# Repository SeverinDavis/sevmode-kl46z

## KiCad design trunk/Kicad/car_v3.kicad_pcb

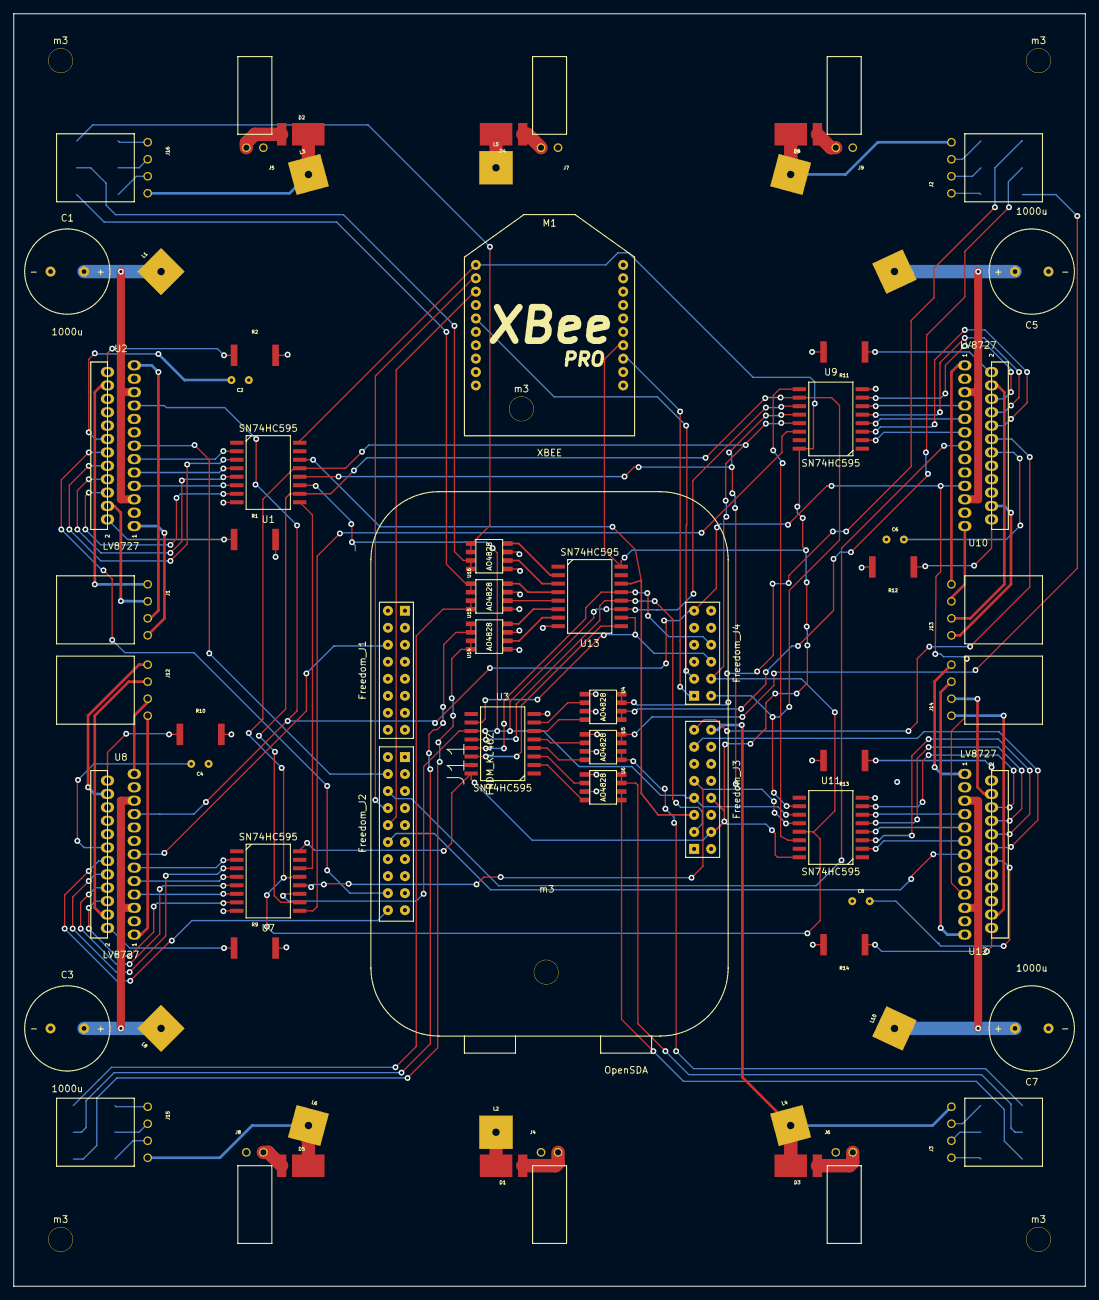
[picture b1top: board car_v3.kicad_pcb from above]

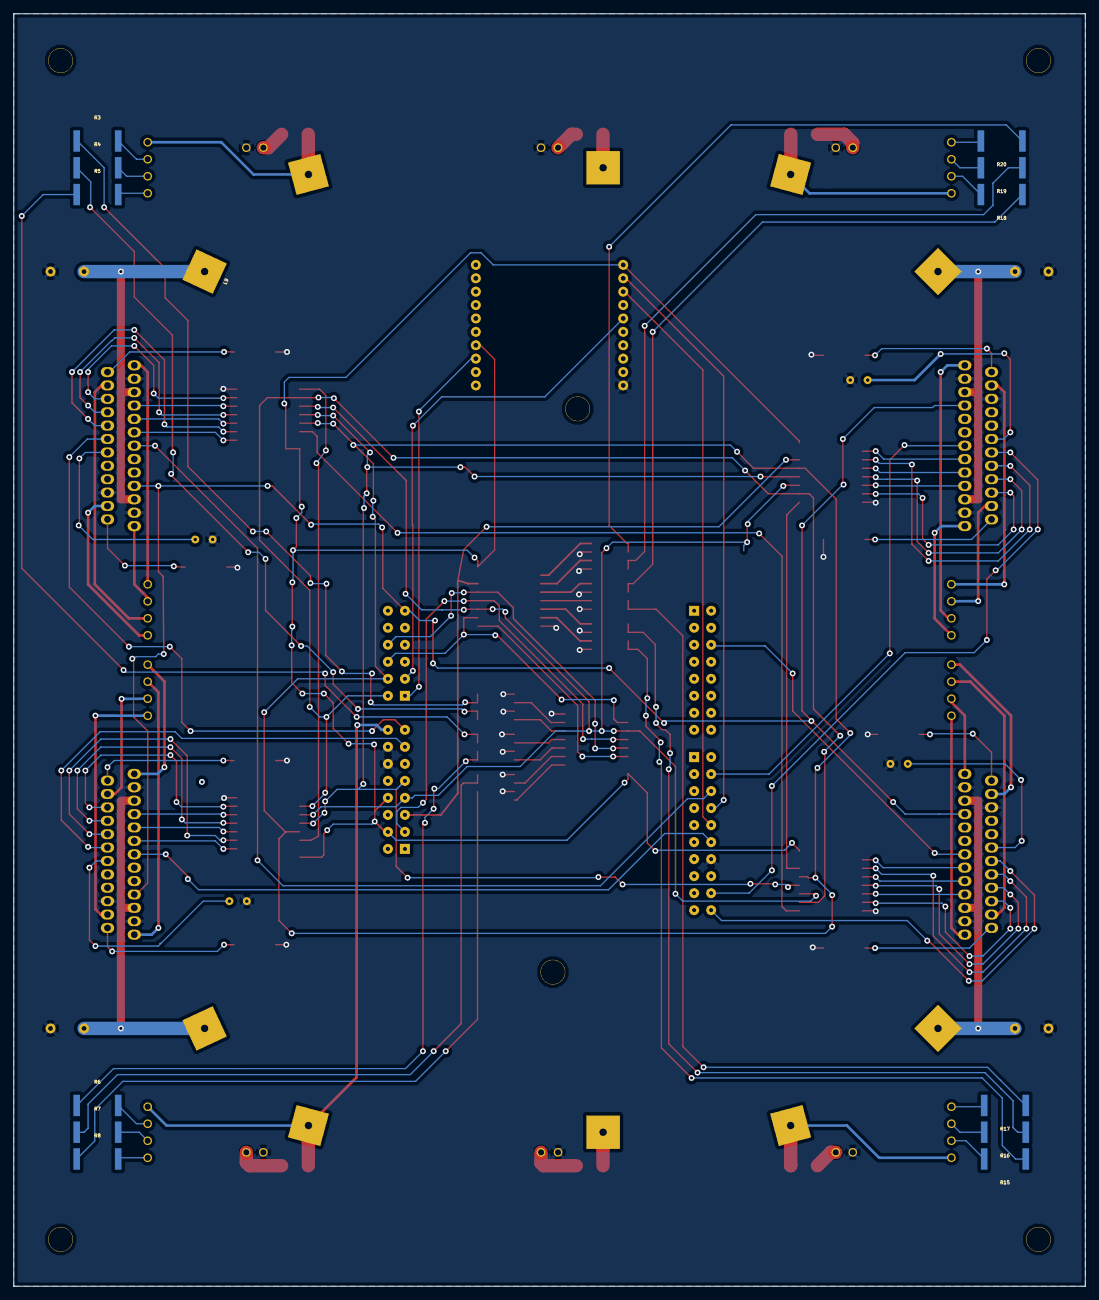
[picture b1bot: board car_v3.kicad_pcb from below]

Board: 2 copper layers, 160.0 x 190.0 mm, 82 parts (13 on the bottom side), 126 nets.

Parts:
C1, C3, C5, C7: 1000u; CAP_1000uF
C2, C4, C6, C8: 180p; __CAP_180p
D1, D2, D3, D4, D5, D6: POWER_DIODE; __POWERDI5
J1, J12, J13, J14: CONN_MOTOR; __4P_CONNECTOR
J2, J3, J15, J16: CONN_LED; __4P_CONNECTOR
J4, J5, J6, J7, J8, J9: CONN2; __2P_CONNECTOR
J11: FRDM_KL46Z; __Freedom
L1, L2, L3, L4, L5, L6, L7, L8, L9, L10: LUG; __LUG
M1: XBEE; __XBeePro
R1, R2, R9, R10, R11, R12, R13, R14: 0.27; _RES
R3, R6, R15, R18: 300; _RES
R4, R5, R7, R8, R16, R17, R19, R20: 249; _RES
U1, U3, U7, U9, U11, U13: SN74HC595; __SN74HC595
U2, U8, U10, U12: LV8727; __LV8728
U4, U5, U6, U14, U15, U16: AO4828; __AO4828
m3, m3#2, m3#3, m3#4, m3#5, m3#6: __m3

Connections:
+3.3V: J11.304, J11.308, M1.1, M1.14, U1.16, U3.16, U7.16, U9.16, U11.16, U13.16
+8V: D1.2, D2.2, D3.2, D4.2, D5.2, D6.2, J2.1, J3.1, J11.316, J15.1, J16.1, L2.1, L3.1, L4.1, L5.1, L6.1, L7.1
/KL46Z_DUAL/L_OE_b: J11.408, U3.13, U13.13
/KL46Z_DUAL/L_SRCLR_b: J11.406, U3.10, U13.10
/KL46Z_DUAL/M0_STEP: J11.204, U2.13
/KL46Z_DUAL/M1_STEP: J11.106, U8.13
/KL46Z_DUAL/M2_STEP: J11.206, U10.13
/KL46Z_DUAL/M3_STEP: J11.212, U12.13
/KL46Z_DUAL/M_OE_b: J11.404, U1.13, U7.13, U9.13, U11.13
/KL46Z_DUAL/M_SRCLR_b: J11.402, U1.10, U7.10, U9.10, U11.10
/KL46Z_DUAL/M_VREF: J11.411, U2.19, U8.19, U10.19, U12.19
/KL46Z_DUAL/SCL: J11.307, U1.11, U3.11, U7.11, U9.11, U11.11, U13.11
/KL46Z_DUAL/SDATA: J11.305, U1.14, U13.14
/LED_DUAL_DRIVER0/CS: J11.303, U3.12, U13.12
/LED_DUAL_DRIVER1/SDIN: U3.14, U13.9
/MOTOR0/CS: J11.309, U1.12, U7.12, U9.12, U11.12
/MOTOR0/FR: J11.218, U2.12
/MOTOR1/FR: J11.220, U8.12
/MOTOR1/SDIN: U1.9, U7.14
/MOTOR2/FR: J11.315, U10.12
/MOTOR2/SDIN: U7.9, U9.14
/MOTOR3/FR: J11.313, U12.12
/MOTOR3/SDIN: U9.9, U11.14
/XBEE0/ON: J11.401, M1.13
/XBEE0/RESET_b: J11.403, M1.5
/XBEE0/RX: J11.208, M1.2
/XBEE0/TX: J11.210, M1.3
GND: C1.2, C2.2, C3.2, C4.2, C5.2, C6.2, C7.2, C8.2, J4.2, J5.2, J6.2, J7.2, J8.2, J9.2, J11.214, J11.312, J11.314, M1.10, R1.2, R2.2, R9.2, R10.2, R11.2, R12.2, R13.2, R14.2, U1.8, U2.3, U2.20, U2.23, U3.8, U4.1, U4.3, U5.1, U5.3, U6.1, U6.3, U7.8, U8.3, U8.20, U8.23, U9.8, U10.3, U10.20, U10.23, U11.8, U12.3, U12.20, U12.23, U13.8, U14.1, U14.3, U15.1, U15.3, U16.1, U16.3
unnamed: J1.1, U2.1
unnamed: C2.1, U2.14
unnamed: J1.3, U2.4
unnamed: U1.7, U2.6
unnamed: J1.2, U2.25
unnamed: J1.4, U2.22
unnamed: R2.1, U2.24
unnamed: U1.4, U2.9
unnamed: R1.1, U2.2
unnamed: U1.6, U2.7
unnamed: U1.5, U2.8
unnamed: U1.3, U2.10
unnamed: U1.2, U2.11
unnamed: C1.1, L1.1, U2.5, U2.21
unnamed: R7.1, U6.5, U6.6
unnamed: R3.1, U4.5, U4.6
unnamed: R4.1, U4.7, U4.8
unnamed: R8.1, U6.7, U6.8
unnamed: J3.3, R7.2
unnamed: J2.2, R3.2
unnamed: J2.3, R4.2
unnamed: J2.4, R5.2
unnamed: J3.2, R6.2
unnamed: J3.4, R8.2
unnamed: U3.2, U6.4
unnamed: U3.3, U6.2
unnamed: U3.4, U5.4
unnamed: U3.7, U4.2
unnamed: U3.6, U4.4
unnamed: U3.5, U5.2
unnamed: R5.1, U5.5, U5.6
unnamed: R6.1, U5.7, U5.8
unnamed: D1.1, J4.1
unnamed: D2.1, J5.1
unnamed: D3.1, J6.1
unnamed: D4.1, J7.1
unnamed: D5.1, J8.1
unnamed: D6.1, J9.1
unnamed: J12.3, U8.4
unnamed: J12.1, U8.1
unnamed: C4.1, U8.14
unnamed: C3.1, L8.1, U8.5, U8.21
unnamed: U7.7, U8.6
unnamed: J12.2, U8.25
unnamed: J12.4, U8.22
unnamed: R10.1, U8.24
unnamed: U7.3, U8.10
unnamed: R9.1, U8.2
unnamed: U7.6, U8.7
unnamed: U7.5, U8.8
unnamed: U7.4, U8.9
unnamed: U7.2, U8.11
unnamed: J13.3, U10.4
unnamed: J13.1, U10.1
unnamed: C6.1, U10.14
unnamed: J13.2, U10.25
unnamed: J13.4, U10.22
unnamed: U9.7, U10.6
unnamed: R12.1, U10.24
unnamed: U9.5, U10.8
unnamed: R11.1, U10.2
unnamed: U9.6, U10.7
unnamed: U9.4, U10.9
unnamed: U9.3, U10.10
unnamed: U9.2, U10.11
unnamed: C5.1, L9.1, U10.5, U10.21
unnamed: J14.3, U12.4
unnamed: J14.1, U12.1
unnamed: C8.1, U12.14
unnamed: U11.7, U12.6
unnamed: J14.2, U12.25
unnamed: J14.4, U12.22
unnamed: R14.1, U12.24
unnamed: U11.5, U12.8
unnamed: R13.1, U12.2
unnamed: U11.6, U12.7
unnamed: U11.4, U12.9
unnamed: U11.3, U12.10
unnamed: U11.2, U12.11
unnamed: C7.1, L10.1, U12.5, U12.21
unnamed: R15.1, U14.5, U14.6
unnamed: R16.1, U14.7, U14.8
unnamed: R19.1, U16.5, U16.6
unnamed: R20.1, U16.7, U16.8
unnamed: J15.2, R15.2
unnamed: J15.3, R16.2
unnamed: J15.4, R17.2
unnamed: J16.2, R18.2
unnamed: J16.3, R19.2
unnamed: J16.4, R20.2
unnamed: U13.2, U16.4
unnamed: U13.3, U16.2
unnamed: U13.4, U15.4
unnamed: U13.7, U14.2
unnamed: U13.6, U14.4
unnamed: U13.5, U15.2
unnamed: R17.1, U15.5, U15.6
unnamed: R18.1, U15.7, U15.8

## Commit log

2014-04-22 Initial directory structure.
2014-05-09 gpio should be working now
2014-05-10 uc_led should be working now
2014-05-11 uc_lptmr.c should work.
    Some weirdness in uc_lptmr_delay:
    Sometimes LED just gets stuck on. Works after power cycling board. So it might be a reset issue or some logic problem.
2014-06-08 All wired. ERC passes with no errors. Might be good to go.
2014-06-08 added lines for m_srclr_b, l_srclr_b, and m_oe_b and l_oe_b. woooot.
2014-06-08 dac working
2014-06-09 pit should be working. nvic needs attention and pit needs to be generalized.
2014-06-09 pit generalized. pit1 and pit0 confirmed as working.
2014-06-19 gpio buggy bug fixed. Also spi1 is semi-usable now. should be. maybe. i think.
2014-06-21 output compare sort of working. uart source and header added.
2014-07-27 pcb seems about done.
2014-08-06 pcb routing. choo choo. chugging along.
2014-08-06 shoot me plz. so many traces...
2014-08-08 All aboard the choo choo shoe.
2014-08-09 pcb might be done.
2014-09-01 Added Visual Studio project with prototype xbox controller/serial port code.
2014-10-13 LED code moved to CAR_LED.c. Not tested yet, but no reason to suspect it wouldn't.
    CAR_MOTOR.c created. Need to copy over code currently in main and plop it into here.
    Also, Kill Paris is pretty dope. Especially at 2:46 AM.
2014-10-13 main includes example of how to use CAR_LED.c
2014-11-01 No longer need dummy sends to get SPI working. Fixed! WOOOO! Motor drivers next!
2014-11-01 preliminary CAR_MOTOR stuff written. Next step is to confirm bit order from sh_regs to mdrivers/ write setter methods to update mdrivers settings.
2014-11-01 motor shift registers should be working now. just need to make the setters.
2014-11-02 filling in more motor driver functions
2014-11-02 motor_startup written and seems to work. need to add and test dac
2014-11-02 dac hardcoding switched to lower current output.
2014-11-09 starting to build xbee/uart stuff
2014-11-14 untested UART and xbee. Some change just caused UART callback to happen, but I don't know what.
2014-11-16 UART working!!! OSR bits in the baud rate denominator weren't being factored in! DUH! #SHREKT
2014-11-22 tpm module working, somewhat tested.
2014-11-26 trying to get pin interrupts on portc and d working.
2014-12-02 button interrupts working w/ example
2014-12-03 stepper motor demo.
2014-12-14 adding function headers
2014-12-18 preliminary stepping acceleration algo. untested.
2014-12-20 working positive acceleration on tpm0 channel 2. neg acceleration still borked.
2014-12-25 switching to lookup table acceleration and deceleration.
2014-12-26 untested acceleration
2014-12-27 rewrote motor callback
2014-12-27 accel and decel working when directions are equal. need to test opposite direction behavior.
2014-12-28 direction reversal working, I think. Next: wakeup high period for fast response.
2014-12-31 generalized period compute code. needs testing though.
2014-12-31 generalized period computation function tested and working
2015-01-05 tentative code for wakeup functionality
2015-01-19 not working atm
2015-01-20 moving motor wakeup functionality to tpm channel 1.
2015-01-23 wakeup written. sort of tested. seems to work.
2015-01-25 Host can send packets to vehicle now. AFAIK packets are assembled correctly at vehicle, but needs confirmation.
2015-01-25 fix uart priority
2015-02-08 couple of little tweaks
2015-02-12 cleaning and formatting
2015-02-13 more cleaning
2015-02-15 formatting and changed acceleration curve
2015-03-04 added failure tolerance on XBee
2015-04-06 Migrating wiki contents from Google Code
2015-04-10 i2c
    adding i2c files
2015-04-10 deleted i2c
2018-04-11 Added Report pdf
    Apparently I never added this to github. Oops.
2018-04-11 Revert "Added Report pdf"
    This reverts commit e2916032b5d37d9b1f373b71a609f67883ea641c.
2018-04-11 Revert "Revert "Added Report pdf""
    This reverts commit 166c0ac29fa0df4e19dead1835c81f141a0e3fa9.
